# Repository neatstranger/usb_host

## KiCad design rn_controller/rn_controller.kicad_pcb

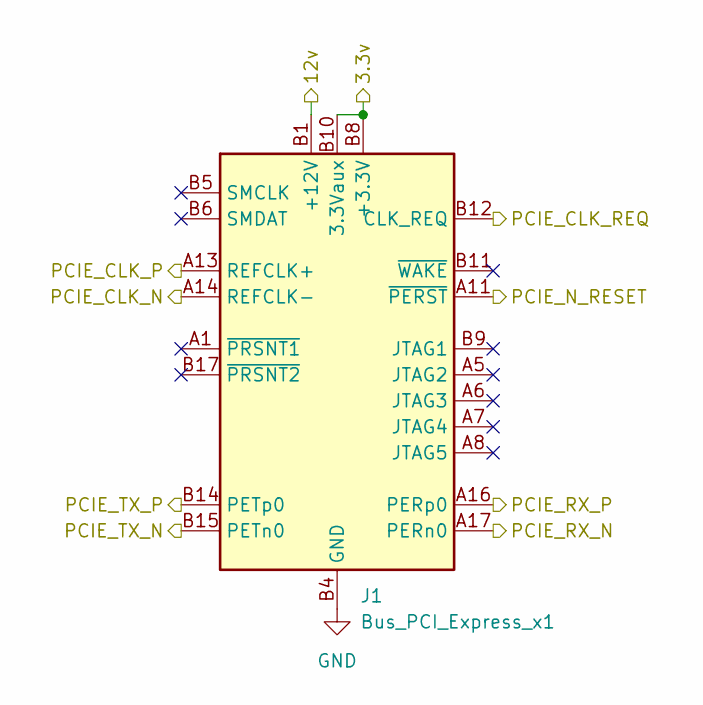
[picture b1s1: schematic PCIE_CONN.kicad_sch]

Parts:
J1: Bus_PCI_Express_x1; BUS_PCIexpress_x1

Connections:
/PCIE_CONN/3.3v: J1.A9 (+3.3V), J1.A10 (+3.3V), J1.B8 (+3.3V), J1.B10 (3.3Vaux); also elsewhere on the board
/PCIE_CONN/12v: J1.A2 (+12V), J1.A3 (+12V), J1.B1 (+12V), J1.B2 (+12V), J1.B3 (+12V); also elsewhere on the board
/PCIE_CONN/PCIE_CLK_N: J1.A14 (REFCLK-); also elsewhere on the board
/PCIE_CONN/PCIE_CLK_P: J1.A13 (REFCLK+); also elsewhere on the board
/PCIE_CONN/PCIE_CLK_REQ: J1.B12 (CLK_REQ); also elsewhere on the board
/PCIE_CONN/PCIE_N_RESET: J1.A11 (~PERST); also elsewhere on the board
/PCIE_CONN/PCIE_RX_N: J1.A17 (PERn0); also elsewhere on the board
/PCIE_CONN/PCIE_RX_P: J1.A16 (PERp0); also elsewhere on the board
/PCIE_CONN/PCIE_TX_N: J1.B15 (PETn0); also elsewhere on the board
/PCIE_CONN/PCIE_TX_P: J1.B14 (PETp0); also elsewhere on the board
GND: J1.A4 (GND), J1.A12 (GND), J1.A15 (GND), J1.A18 (GND), J1.B4 (GND), J1.B7 (GND), J1.B13 (GND), J1.B16 (GND), J1.B18 (GND); also elsewhere on the board

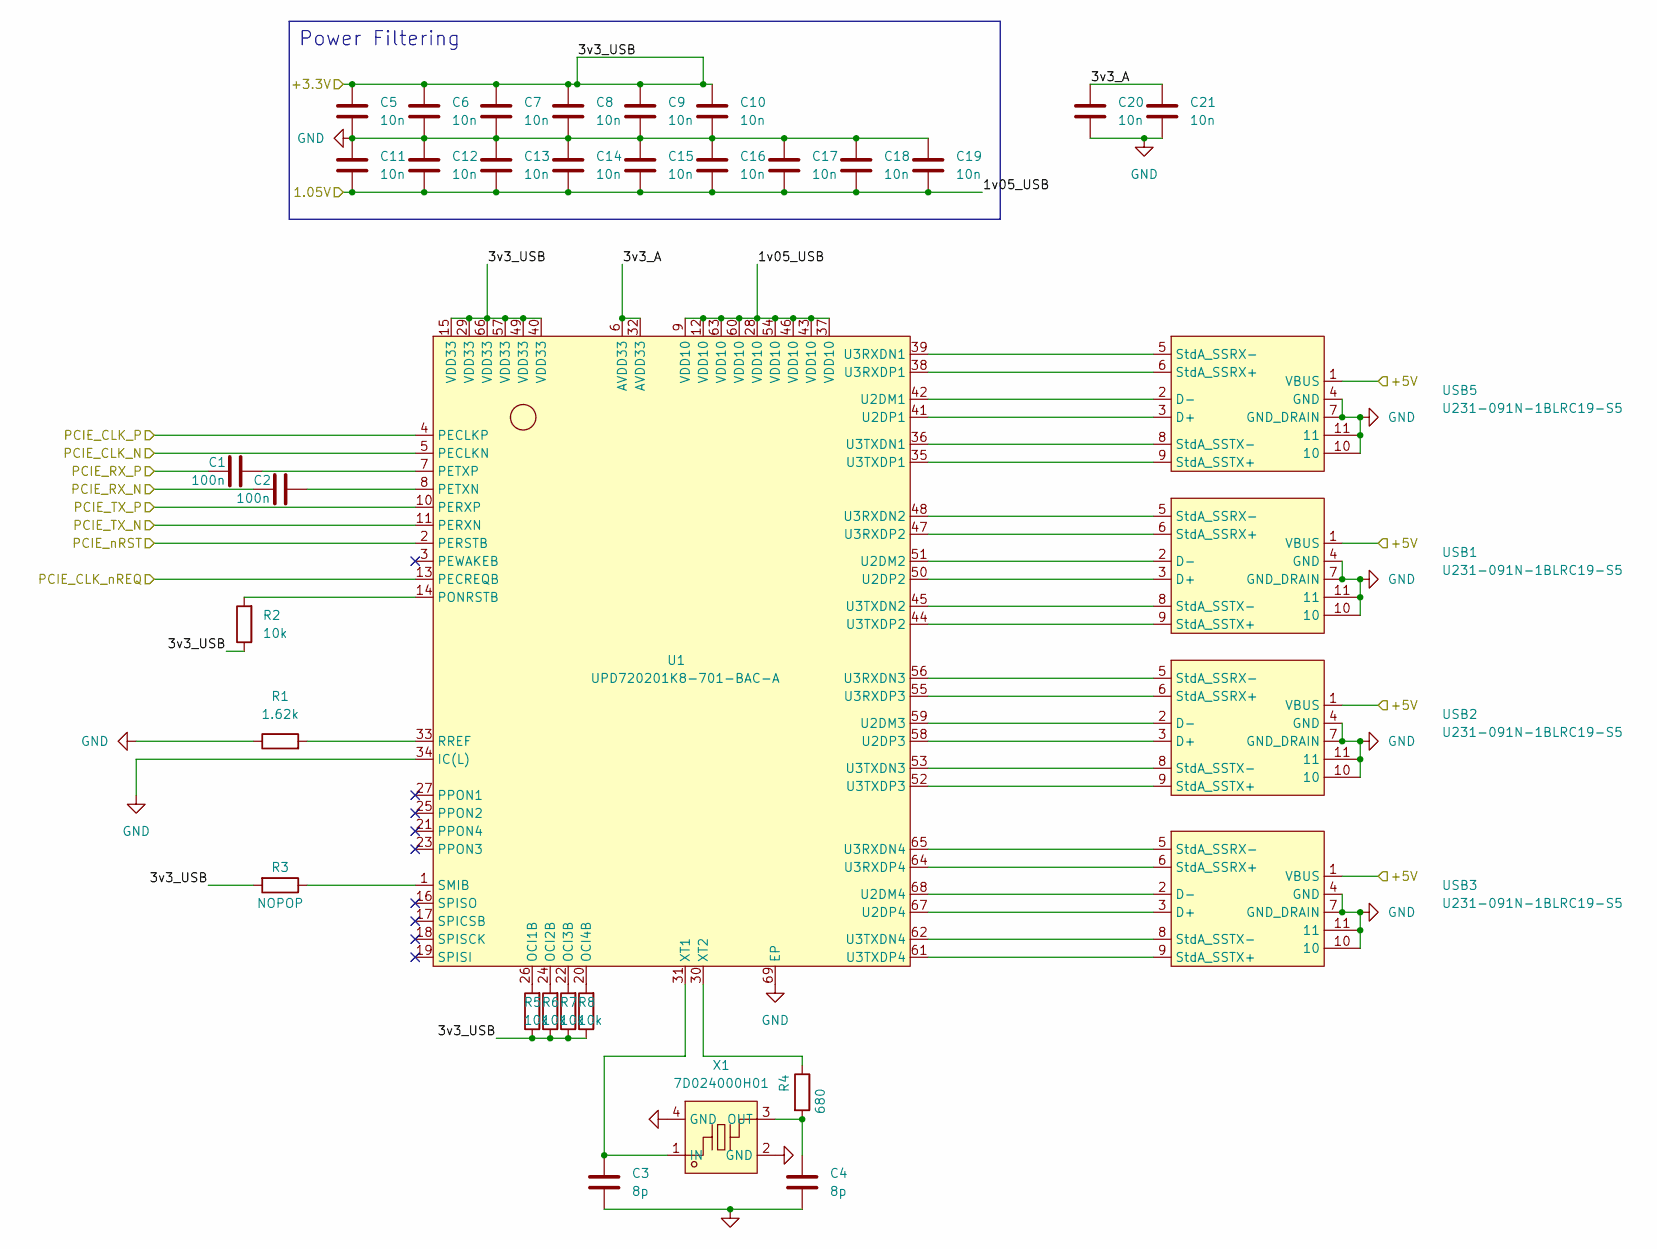
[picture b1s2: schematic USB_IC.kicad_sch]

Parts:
C1, C2: 100n; R_0402_1005Metric; LCSC Part C312123
C3, C4: 8p; R_0402_1005Metric; LCSC Part C962144
C5, C6, C7, C8, C9, C10, C11, C12, C13, C14, C15, C16, C17, C18, C19, C20, C21: 10n; R_0402_1005Metric; LCSC Part C525224
R1: 1.62k; R_0402_1005Metric; LCSC Part C830229
R2, R5, R6, R7, R8: 10k; R_0402_1005Metric; LCSC Part C163810
R3: NOPOP; R_0402_1005Metric
R4: 680; R_0402_1005Metric; LCSC Part C137948
U1: UPD720201K8-701-BAC-A; QFN-68_L8.0-W8.0-P0.40-BL-EP6.2; LCSC Part C355375
USB1, USB2, USB3, USB5: U231-091N-1BLRC19-S5; USB-A-TH_U231-091N-1BLRC19-S5; LCSC Part C908473
X1: 7D024000H01; CRYSTAL-SMD_4P-L2.0-W1.6-BL; LCSC Part C648933

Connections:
/PCIE_CONN/PCIE_CLK_N: U1.5 (PECLKN); also elsewhere on the board
/PCIE_CONN/PCIE_CLK_P: U1.4 (PECLKP); also elsewhere on the board
/PCIE_CONN/PCIE_CLK_REQ: U1.13 (PECREQB); also elsewhere on the board
/PCIE_CONN/PCIE_N_RESET: U1.2 (PERSTB); also elsewhere on the board
/PCIE_CONN/PCIE_RX_N: C2.1; also elsewhere on the board
/PCIE_CONN/PCIE_RX_P: C1.1; also elsewhere on the board
/PCIE_CONN/PCIE_TX_N: U1.11 (PERXN); also elsewhere on the board
/PCIE_CONN/PCIE_TX_P: U1.10 (PERXP); also elsewhere on the board
/PSU/5V: USB1.1 (VBUS), USB2.1 (VBUS), USB3.1 (VBUS), USB5.1 (VBUS); also elsewhere on the board
/USB_IC/1v05_USB: C11.2, C12.2, C13.2, C14.2, C15.2, C16.2, C17.2, C18.2, C19.2, U1.9 (VDD10), U1.12 (VDD10), U1.28 (VDD10), U1.37 (VDD10), U1.43 (VDD10), U1.46 (VDD10), U1.54 (VDD10), U1.60 (VDD10), U1.63 (VDD10); also elsewhere on the board
/USB_IC/3v3_A: C20.1, C21.1, U1.6 (AVDD33), U1.32 (AVDD33)
/USB_IC/3v3_USB: C5.1, C6.1, C7.1, C8.1, C9.1, C10.1, R2.1, R3.2, R5.1, R6.1, R7.1, R8.1, U1.15 (VDD33), U1.29 (VDD33), U1.40 (VDD33), U1.49 (VDD33), U1.57 (VDD33), U1.66 (VDD33); also elsewhere on the board
GND: C3.2, C4.2, C5.2, C6.2, C7.2, C8.2, C9.2, C10.2, C11.1, C12.1, C13.1, C14.1, C15.1, C16.1, C17.1, C18.1, C19.1, C20.2, C21.2, R1.1, U1.34 (IC(L)), U1.69 (EP), USB1.4 (GND), USB1.7 (GND_DRAIN), USB1.10, USB1.11, USB2.4 (GND), USB2.7 (GND_DRAIN), USB2.10, USB2.11, USB3.4 (GND), USB3.7 (GND_DRAIN), USB3.10, USB3.11, USB5.4 (GND), USB5.7 (GND_DRAIN), USB5.10, USB5.11, X1.2 (GND), X1.4 (GND); also elsewhere on the board
unnamed: R5.2, U1.26 (OCI1B)
unnamed: R6.2, U1.24 (OCI2B)
unnamed: R7.2, U1.22 (OCI3B)
unnamed: R8.2, U1.20 (OCI4B)
unnamed: C2.2, U1.8 (PETXN)
unnamed: C1.2, U1.7 (PETXP)
unnamed: R2.2, U1.14 (PONRSTB)
unnamed: R1.2, U1.33 (RREF)
unnamed: R3.1, U1.1 (SMIB)
unnamed: U1.42 (U2DM1), USB5.2 (D-)
unnamed: U1.51 (U2DM2), USB1.2 (D-)
unnamed: U1.59 (U2DM3), USB2.2 (D-)
unnamed: U1.68 (U2DM4), USB3.2 (D-)
unnamed: U1.41 (U2DP1), USB5.3 (D+)
unnamed: U1.50 (U2DP2), USB1.3 (D+)
unnamed: U1.58 (U2DP3), USB2.3 (D+)
unnamed: U1.67 (U2DP4), USB3.3 (D+)
unnamed: U1.39 (U3RXDN1), USB5.5 (StdA_SSRX-)
unnamed: U1.48 (U3RXDN2), USB1.5 (StdA_SSRX-)
unnamed: U1.56 (U3RXDN3), USB2.5 (StdA_SSRX-)
unnamed: U1.65 (U3RXDN4), USB3.5 (StdA_SSRX-)
unnamed: U1.38 (U3RXDP1), USB5.6 (StdA_SSRX+)
unnamed: U1.47 (U3RXDP2), USB1.6 (StdA_SSRX+)
unnamed: U1.55 (U3RXDP3), USB2.6 (StdA_SSRX+)
unnamed: U1.64 (U3RXDP4), USB3.6 (StdA_SSRX+)
unnamed: U1.36 (U3TXDN1), USB5.8 (StdA_SSTX-)
unnamed: U1.45 (U3TXDN2), USB1.8 (StdA_SSTX-)
unnamed: U1.53 (U3TXDN3), USB2.8 (StdA_SSTX-)
unnamed: U1.62 (U3TXDN4), USB3.8 (StdA_SSTX-)
unnamed: U1.35 (U3TXDP1), USB5.9 (StdA_SSTX+)
unnamed: U1.44 (U3TXDP2), USB1.9 (StdA_SSTX+)
unnamed: U1.52 (U3TXDP3), USB2.9 (StdA_SSTX+)
unnamed: U1.61 (U3TXDP4), USB3.9 (StdA_SSTX+)
unnamed: C3.1, U1.31 (XT1), X1.1 (IN)
unnamed: R4.1, U1.30 (XT2)
unnamed: C4.1, R4.2, X1.3 (OUT)

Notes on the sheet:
Power Filtering

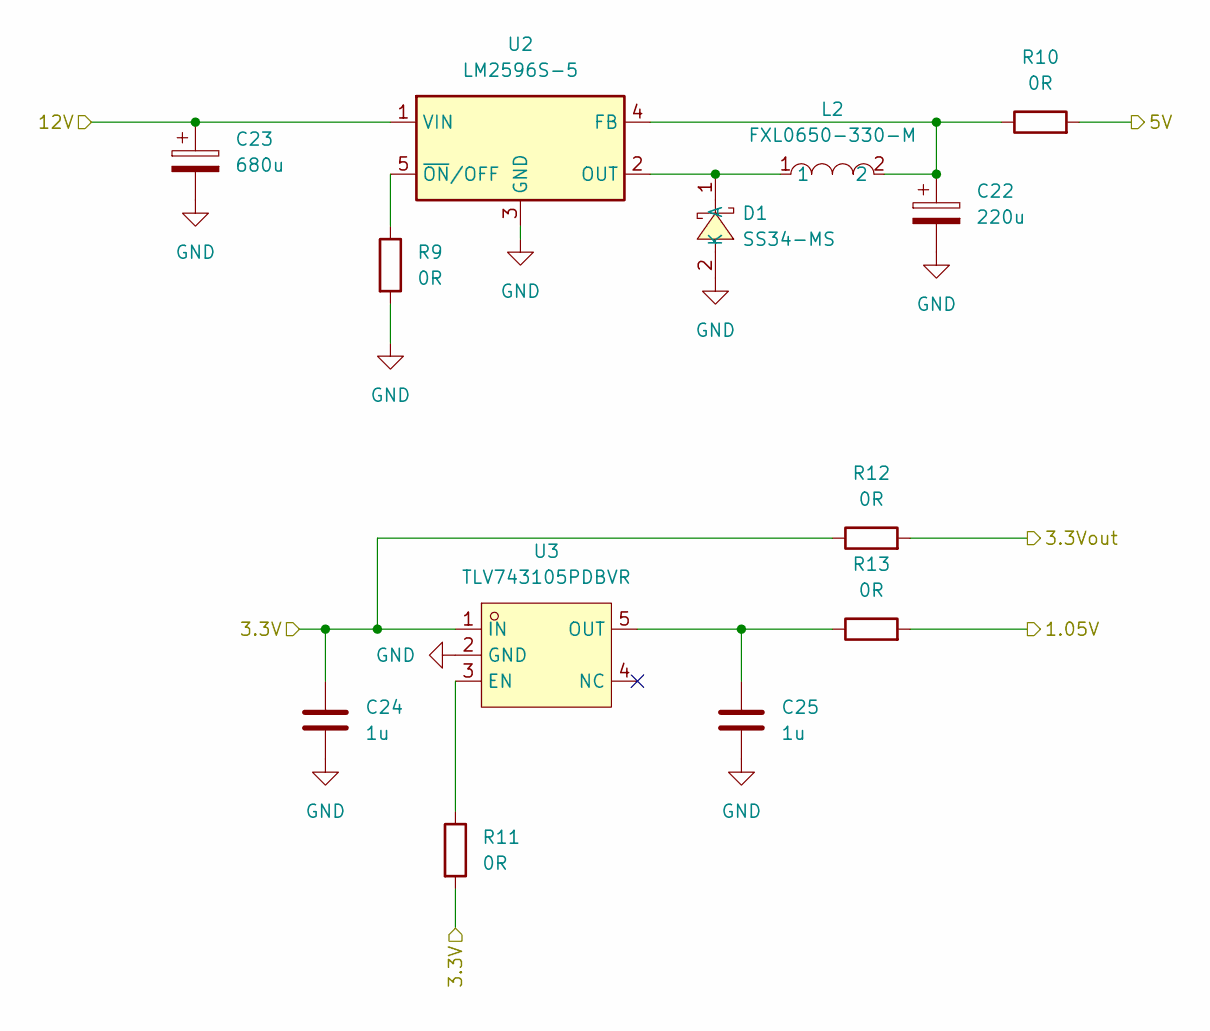
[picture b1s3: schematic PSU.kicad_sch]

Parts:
C22: 220u; CP_Elec_6.3x7.7; LCSC Part C497598
C23: 680u; CP_Elec_10x10.5; LCSC Part C497598
C24, C25: 1u; R_0402_1005Metric; LCSC Part C77006
D1: SS34-MS; DO-214AC_L4.3-W2.7-LS5.0-RD; LCSC Part C2836396
L2: FXL0650-330-M; IND-SMD_L7.0-W6.6_FXL0650; LCSC Part C475526
R9, R10, R11, R12, R13: 0R; R_0805_2012Metric; LCSC Part C304192
U2: LM2596S-5; TO-263-5_TabPin3; LCSC Part C347421
U3: TLV743105PDBVR; SOT-23-5_L3.0-W1.7-P0.95-LS2.8-BL; LCSC Part C469896

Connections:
/PCIE_CONN/3.3v: C24.1, R11.2, R12.1, U3.1 (IN); also elsewhere on the board
/PCIE_CONN/12v: C23.1, U2.1 (VIN); also elsewhere on the board
/PSU/5V: R10.2; also elsewhere on the board
/USB_IC/1v05_USB: R13.2; also elsewhere on the board
/USB_IC/3v3_USB: R12.2; also elsewhere on the board
GND: C22.2, C23.2, C24.2, C25.2, D1.2 (K), R9.2, U2.3 (GND), U3.2 (GND); also elsewhere on the board
unnamed: D1.1 (A), L2.1, U2.2 (OUT)
unnamed: C22.1, L2.2, R10.1, U2.4 (FB)
unnamed: R9.1, U2.5 (~ON/OFF)
unnamed: R11.1, U3.3 (EN)
unnamed: C25.1, R13.1, U3.5 (OUT)

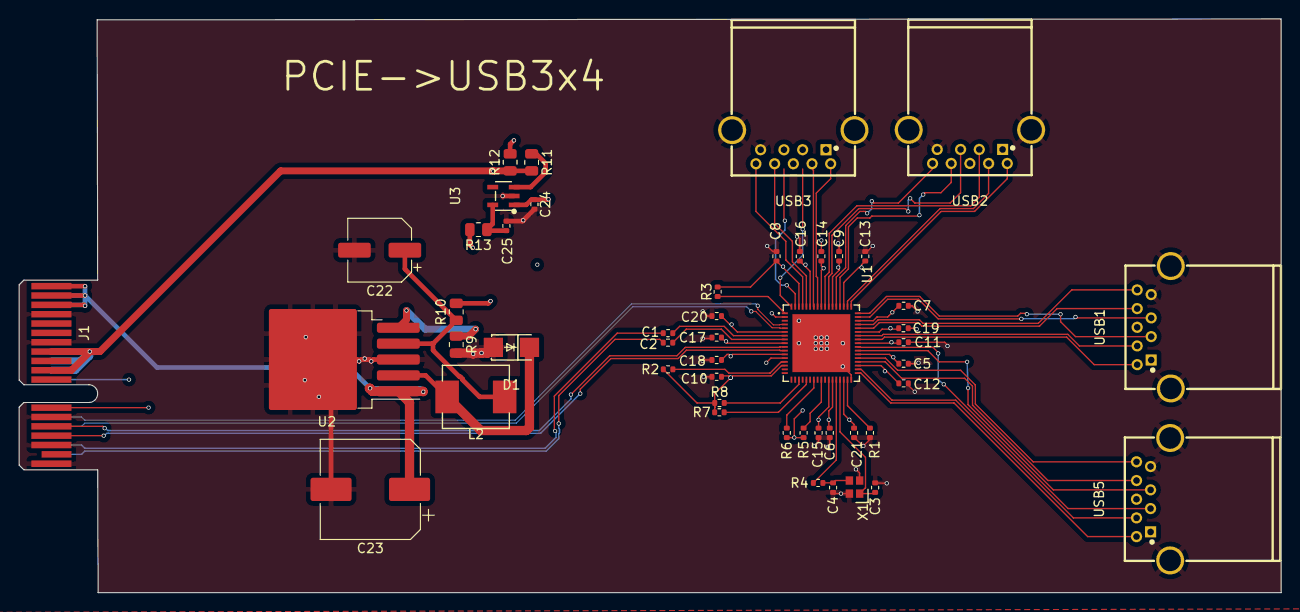
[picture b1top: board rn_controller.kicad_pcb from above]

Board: 6 copper layers, 135.0 x 61.4 mm, 49 parts (0 on the bottom side), 56 nets.

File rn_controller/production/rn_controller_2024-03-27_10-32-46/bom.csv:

Designator,Footprint,Quantity,Value,LCSC Part #
"C1, C2",0402,2,100n,C312123
"C10, C11, C12, C13, C14, C15, C16, C17, C18, C19, C20, C21, C5, C6, C7, C8, C9",0402,17,10n,C525224
C22,CP_Elec_6.3x7.7,1,220u,C497598
C23,CP_Elec_10x10.5,1,680u,C497598
"C24, C25",0402,2,1u,C77006
"C3, C4",0402,2,8p,C962144
D1,DO-214AC_L4.3-W2.7-LS5.0-RD,1,SS34-MS,C2836396
J1,BUS_PCIexpress_x1,1,Bus_PCI_Express_x1,
L2,IND-SMD_L7.0-W6.6_FXL0650,1,FXL0650-330-M,C475526
R1,0402,1,1.62k,C830229
"R10, R11, R12, R13, R9",0805,5,0R,C304192
"R2, R5, R6, R7, R8",0402,5,10k,C163810
R3,0402,1,NOPOP,
R4,0402,1,680,C137948
U1,QFN-68_L8.0-W8.0-P0.40-BL-EP6.2,1,UPD720201K8-701-BAC-A,C355375
U2,TO-263-5_TabPin3,1,LM2596S-5,C347421
U3,SOT-23-5_L3.0-W1.7-P0.95-LS2.8-BL,1,TLV743105PDBVR,C469896
"USB1, USB2, USB3, USB5",USB-A-TH_U231-091N-1BLRC19-S5,4,U231-091N-1BLRC19-S5,C908473
X1,CRYSTAL-SMD_4P-L2.0-W1.6-BL,1,7D024000H01,C648933

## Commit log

2024-03-26 Added Previous Parts library
2024-03-26 Added USB host controller
2024-03-26 Changed layout of UPD720201 symbol
2024-03-26 Working on part selection.
2024-03-27 Finished routing.
2024-03-27 Closeout.
2024-03-27 Fixed capacitor.
